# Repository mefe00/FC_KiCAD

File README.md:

# FC_KiCAD
Projede STM32F405RGT6 MCU, ICM-42688-P IMU, BMP388 basınç sensörü ve istenirse harici takılabilmesi için SPI çıkışı ve I2C çıkışı mevcuttur. Projenin yazılımı github hesabım üzerinde mevcuttur ve geliştirilme aşamasındadır.

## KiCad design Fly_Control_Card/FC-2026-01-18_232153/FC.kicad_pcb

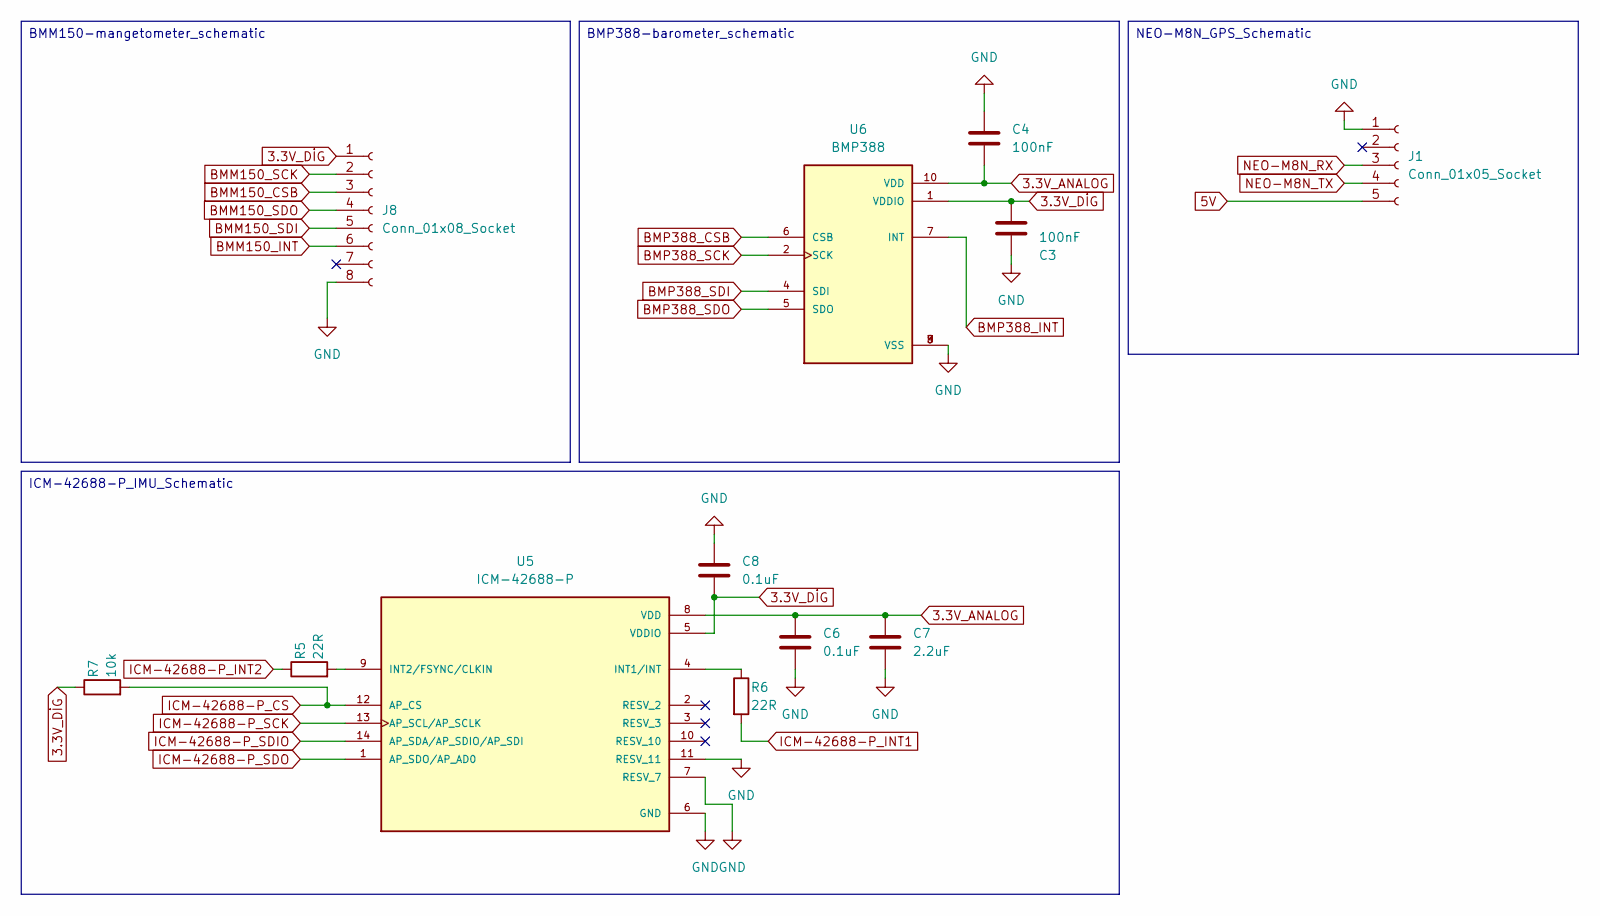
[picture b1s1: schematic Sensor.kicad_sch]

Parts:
C3, C4: 100nF; C_0402_1005Metric
C6, C8: 0.1uF; C_0402_1005Metric
C7: 2.2uF; C_0402_1005Metric
J1: Conn_01x05_Socket; JST_SH_SM05B-SRSS-TB_1x05-1MP_P1.00mm_Horizontal
J8: Conn_01x08_Socket; JST_SH_SM08B-SRSS-TB_1x08-1MP_P1.00mm_Horizontal
R5, R6: 22R; R_0402_1005Metric
R7: 10k; R_0402_1005Metric
U5: ICM-42688-P; PQFN50P300X250X97-14N; PARTREV 1.2
U6: BMP388; PQFN50P200X200X80-10N; PARTREV 1.1

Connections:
3.3V_ANALOG: C4.2, C6.1, C7.1, U5.8 (VDD), U6.10 (VDD); also elsewhere on the board
3.3V_DİG: C3.1, C8.2, J8.1, R7.1, U5.5 (VDDIO), U6.1 (VDDIO); also elsewhere on the board
5V: J1.5; also elsewhere on the board
BMM150_CSB: J8.3; also elsewhere on the board
BMM150_INT: J8.6; also elsewhere on the board
BMM150_SCK: J8.2; also elsewhere on the board
BMM150_SDI: J8.5; also elsewhere on the board
BMM150_SDO: J8.4; also elsewhere on the board
BMP388_CSB: U6.6 (CSB); also elsewhere on the board
BMP388_INT: U6.7 (INT); also elsewhere on the board
BMP388_SCK: U6.2 (SCK); also elsewhere on the board
BMP388_SDI: U6.4 (SDI); also elsewhere on the board
BMP388_SDO: U6.5 (SDO); also elsewhere on the board
GND: C3.2, C4.1, C6.2, C7.2, C8.1, J1.1, J8.8, U5.6 (GND), U5.7 (RESV_7), U5.11 (RESV_11), U6.3 (VSS), U6.8 (VSS), U6.9 (VSS); also elsewhere on the board
ICM-42688-P_CS: R7.2, U5.12 (AP_CS); also elsewhere on the board
ICM-42688-P_INT1: R6.2; also elsewhere on the board
ICM-42688-P_INT2: R5.1; also elsewhere on the board
ICM-42688-P_SCK: U5.13 (AP_SCL/AP_SCLK); also elsewhere on the board
ICM-42688-P_SDIO: U5.14 (AP_SDA/AP_SDIO/AP_SDI); also elsewhere on the board
ICM-42688-P_SDO: U5.1 (AP_SDO/AP_AD0); also elsewhere on the board
NEO-M8N_RX: J1.3; also elsewhere on the board
NEO-M8N_TX: J1.4; also elsewhere on the board
unnamed: R6.1, U5.4 (INT1/INT)
unnamed: R5.2, U5.9 (INT2/FSYNC/CLKIN)

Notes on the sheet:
BMP388-barometer_schematic
NEO-M8N_GPS_Schematic
BMM150-mangetometer_schematic
ICM-42688-P_IMU_Schematic

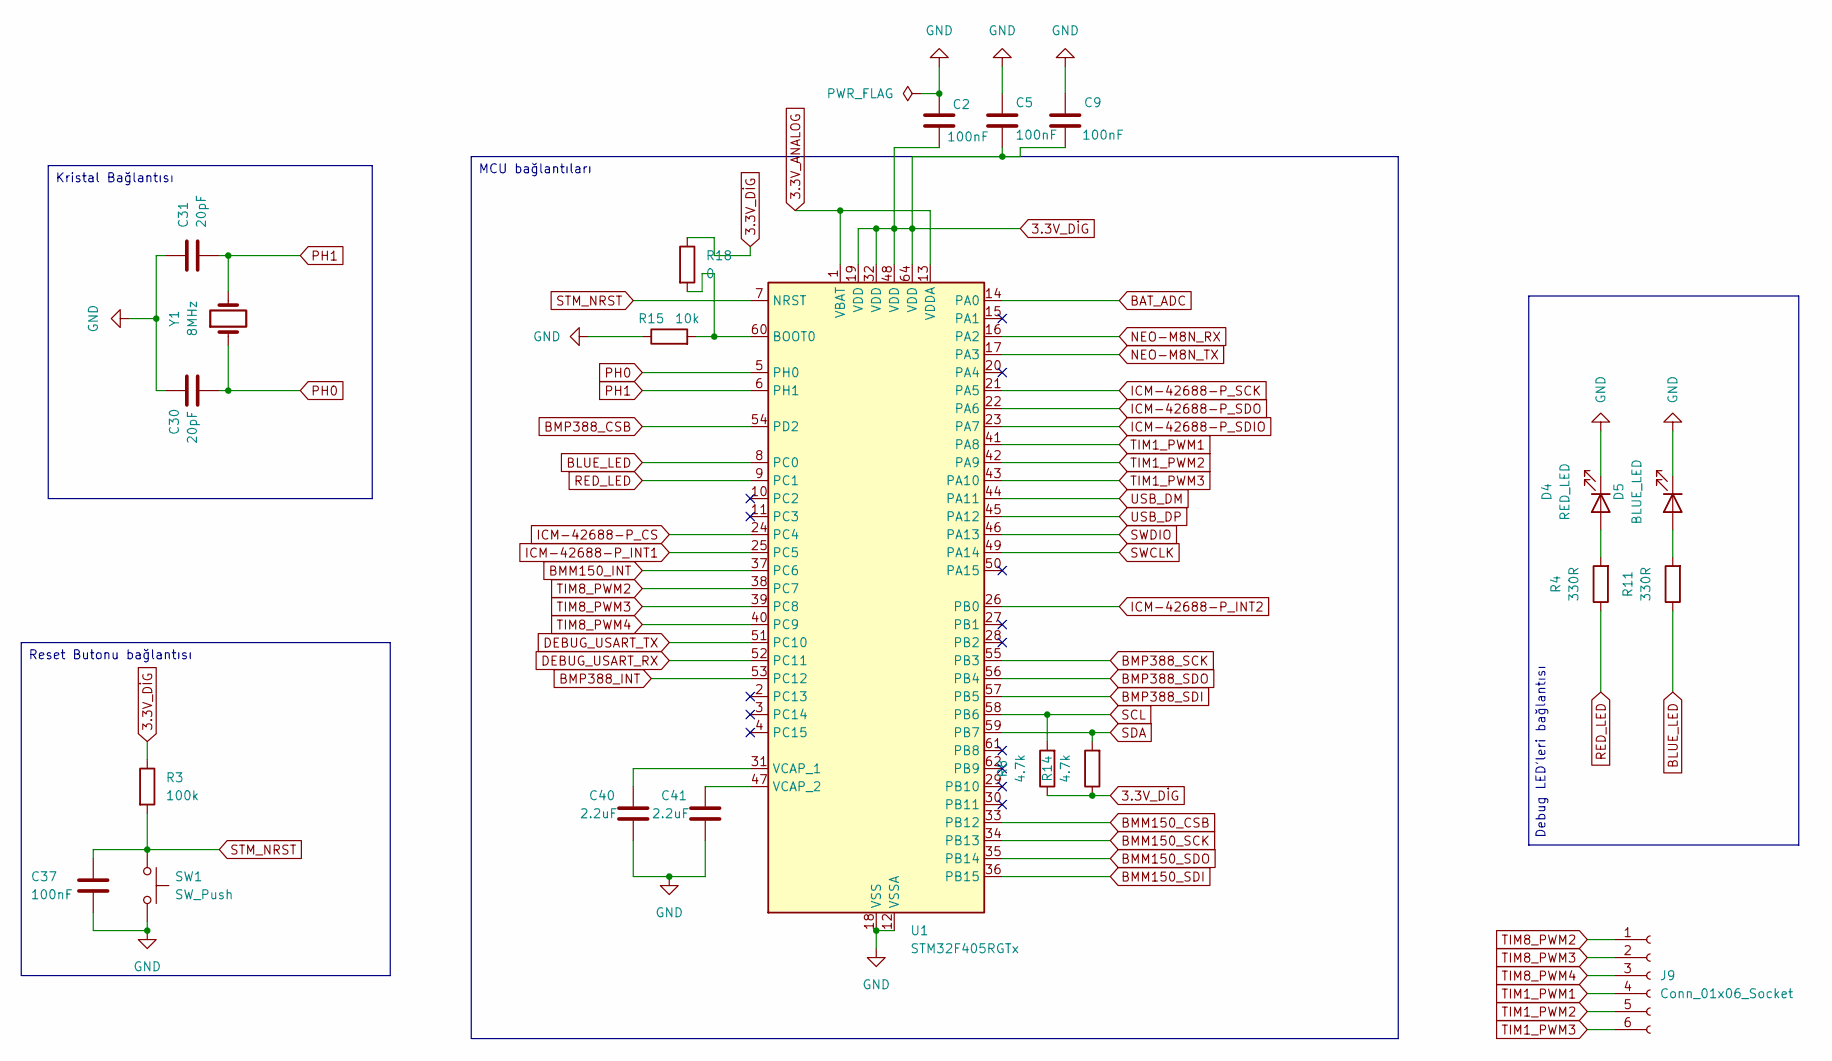
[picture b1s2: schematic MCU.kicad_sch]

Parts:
C2, C5, C9, C37: 100nF; C_0402_1005Metric
C30, C31: 20pF; C_0402_1005Metric
C40, C41: 2.2uF; C_0402_1005Metric
D4: RED_LED; LED_0603_1608Metric
D5: BLUE_LED; LED_0603_1608Metric
J9: Conn_01x06_Socket; JST_SH_SM06B-SRSS-TB_1x06-1MP_P1.00mm_Horizontal
R3: 100k; R_0402_1005Metric
R4, R11: 330R; R_0402_1005Metric
R8, R14: 4.7k; R_0402_1005Metric
R15: 10k; R_0402_1005Metric
R18: 0; R_0402_1005Metric
SW1: SW_Push; SW_Push_1P1T_NO_CK_KMR2
U1: STM32F405RGTx; LQFP-64_10x10mm_P0.5mm
Y1: 8MHz; Crystal_SMD_5032-2Pin_5.0x3.2mm

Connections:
3.3V_ANALOG: U1.1 (VBAT), U1.13 (VDDA); also elsewhere on the board
3.3V_DİG: C2.2, C5.2, C9.2, R3.1, R8.1, R14.1, R18.1, U1.19 (VDD), U1.32 (VDD), U1.48 (VDD), U1.64 (VDD); also elsewhere on the board
BAT_ADC: U1.14 (PA0); also elsewhere on the board
BLUE_LED: R11.1, U1.8 (PC0)
BMM150_CSB: U1.33 (PB12); also elsewhere on the board
BMM150_INT: U1.37 (PC6); also elsewhere on the board
BMM150_SCK: U1.34 (PB13); also elsewhere on the board
BMM150_SDI: U1.36 (PB15); also elsewhere on the board
BMM150_SDO: U1.35 (PB14); also elsewhere on the board
BMP388_CSB: U1.54 (PD2); also elsewhere on the board
BMP388_INT: U1.53 (PC12); also elsewhere on the board
BMP388_SCK: U1.55 (PB3); also elsewhere on the board
BMP388_SDI: U1.57 (PB5); also elsewhere on the board
BMP388_SDO: U1.56 (PB4); also elsewhere on the board
DEBUG_USART_RX: U1.52 (PC11); also elsewhere on the board
DEBUG_USART_TX: U1.51 (PC10); also elsewhere on the board
GND: C2.1, C5.1, C9.1, C30.1, C31.1, C37.2, C40.2, C41.2, D4.1 (K), D5.1 (K), R15.1, SW1.2, U1.12 (VSSA), U1.18 (VSS), U1.63 (VSS); also elsewhere on the board
ICM-42688-P_CS: U1.24 (PC4); also elsewhere on the board
ICM-42688-P_INT1: U1.25 (PC5); also elsewhere on the board
ICM-42688-P_INT2: U1.26 (PB0); also elsewhere on the board
ICM-42688-P_SCK: U1.21 (PA5); also elsewhere on the board
ICM-42688-P_SDIO: U1.23 (PA7); also elsewhere on the board
ICM-42688-P_SDO: U1.22 (PA6); also elsewhere on the board
NEO-M8N_RX: U1.16 (PA2); also elsewhere on the board
NEO-M8N_TX: U1.17 (PA3); also elsewhere on the board
unnamed: D4.2 (A), R4.2
unnamed: D5.2 (A), R11.2
unnamed: R15.2, R18.2, U1.60 (BOOT0)
unnamed: C40.1, U1.31 (VCAP_1)
unnamed: C41.1, U1.47 (VCAP_2)
PH0: C30.2, U1.5 (PH0), Y1.1
PH1: C31.2, U1.6 (PH1), Y1.2
RED_LED: R4.1, U1.9 (PC1)
SCL: R8.2, U1.58 (PB6); also elsewhere on the board
SDA: R14.2, U1.59 (PB7); also elsewhere on the board
STM_NRST: C37.1, R3.2, SW1.1, U1.7 (NRST)
SWCLK: U1.49 (PA14); also elsewhere on the board
SWDIO: U1.46 (PA13); also elsewhere on the board
TIM1_PWM1: J9.4, U1.41 (PA8)
TIM1_PWM2: J9.5, U1.42 (PA9)
TIM1_PWM3: J9.6, U1.43 (PA10)
TIM8_PWM2: J9.1, U1.38 (PC7)
TIM8_PWM3: J9.2, U1.39 (PC8)
TIM8_PWM4: J9.3, U1.40 (PC9)
USB_DM: U1.44 (PA11); also elsewhere on the board
USB_DP: U1.45 (PA12); also elsewhere on the board

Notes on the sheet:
Kristal Bağlantısı
Reset Butonu bağlantısı
Debug LED'leri bağlantısı
MCU bağlantıları

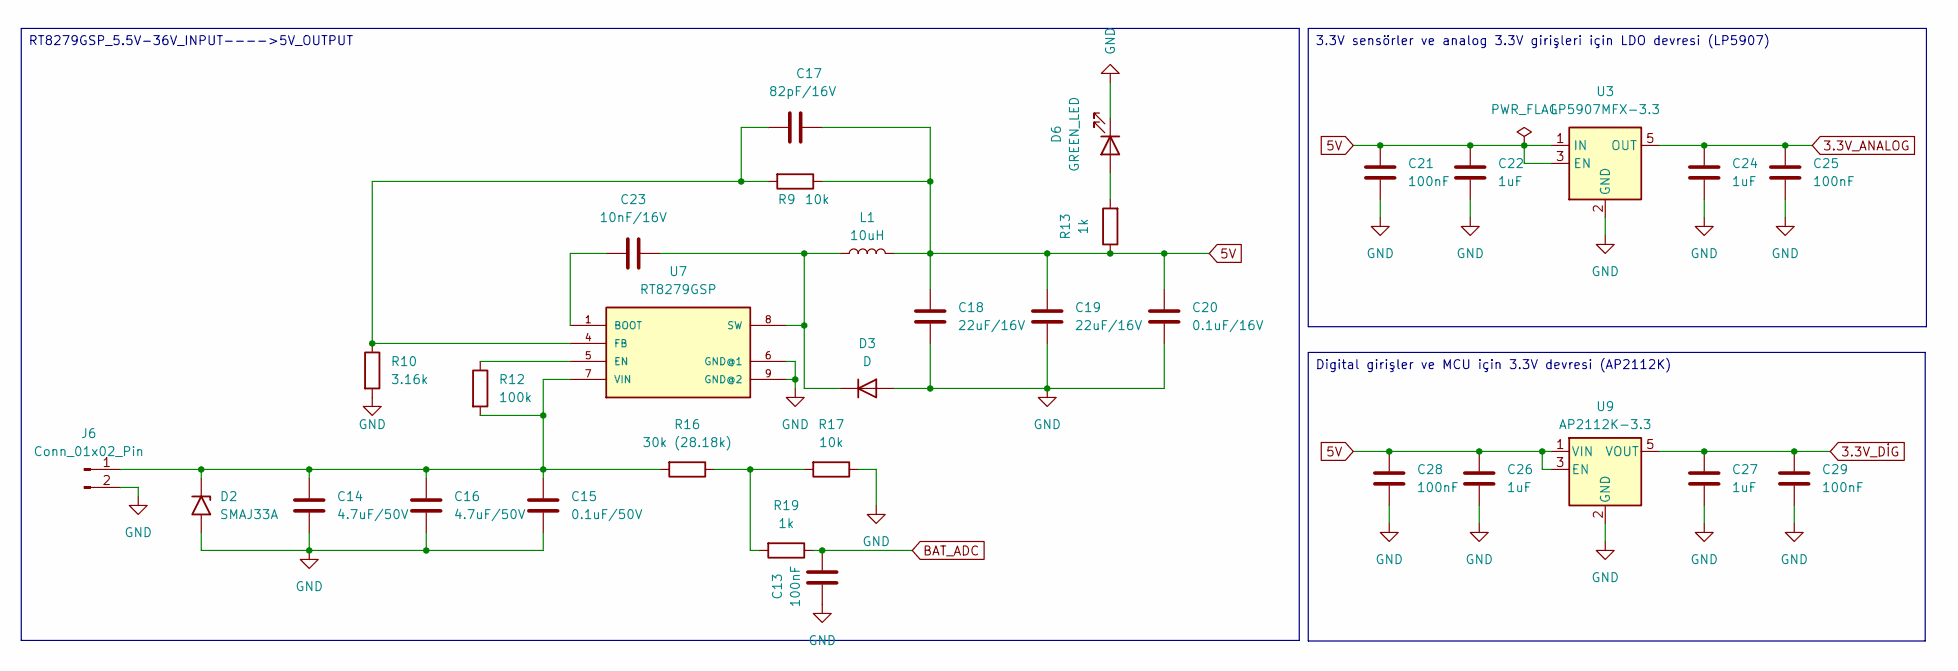
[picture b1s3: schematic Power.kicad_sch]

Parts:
C13, C21, C25, C28, C29: 100nF; C_0603_1608Metric
C14, C16: 4.7uF/50V; C_0603_1608Metric
C15: 0.1uF/50V; C_0603_1608Metric
C17: 82pF/16V; C_0603_1608Metric
C18, C19: 22uF/16V; C_0603_1608Metric
C20: 0.1uF/16V; C_0603_1608Metric
C22, C24, C26, C27: 1uF; C_0402_1005Metric
C23: 10nF/16V; C_0603_1608Metric
D2: SMAJ33A; D_SMA
D3: D; D_SMC
D6: GREEN_LED; LED_0603_1608Metric
J6: Conn_01x02_Pin; SolderWire-0.1sqmm_1x02_P3.6mm_D0.4mm_OD1mm
L1: 10uH; L_APV_ANR4026
R9: 10k; R_0603_1608Metric
R10: 3.16k; R_0603_1608Metric
R12: 100k; R_0603_1608Metric
R13: 1k; R_0402_1005Metric
R16: 30k (28.18k); R_0805_2012Metric
R17: 10k; R_0805_2012Metric
R19: 1k; R_0805_2012Metric
U3: LP5907MFX-3.3; SOT-23-5
U7: RT8279GSP; SOIC127P600X175-9N
U9: AP2112K-3.3; SOT-23-5

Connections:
3.3V_ANALOG: C24.1, C25.1, U3.5 (OUT); also elsewhere on the board
3.3V_DİG: C27.1, C29.1, U9.5 (VOUT); also elsewhere on the board
5V: C17.1, C18.1, C19.1, C20.1, C21.1, C22.1, C26.1, C28.1, L1.2, R9.1, R13.1, U3.1 (IN), U3.3 (EN), U9.1 (VIN), U9.3 (EN); also elsewhere on the board
BAT_ADC: C13.2, R19.1; also elsewhere on the board
GND: C13.1, C14.2, C15.2, C16.2, C18.2, C19.2, C20.2, C21.2, C22.2, C24.2, C25.2, C26.2, C27.2, C28.2, C29.2, D2.2 (A2), D3.2 (A), D6.1 (K), J6.2, R10.2, R17.1, U3.2 (GND), U7.6 (GND@1), U7.9 (GND@2), U9.2 (GND); also elsewhere on the board
unnamed: C14.1, C15.1, C16.1, D2.1 (A1), J6.1, R12.2, R16.2, U7.7 (VIN)
unnamed: C23.2, D3.1 (K), L1.1, U7.8 (SW)
unnamed: D6.2 (A), R13.2
unnamed: R16.1, R17.2, R19.2
unnamed: C23.1, U7.1 (BOOT)
unnamed: R12.1, U7.5 (EN)
unnamed: C17.2, R9.2, R10.1, U7.4 (FB)

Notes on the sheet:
3.3V sensörler ve analog 3.3V girişleri için LDO devresi (LP5907)
RT8279GSP_5.5V-36V_INPUT---->5V_OUTPUT
Digital girişler ve MCU için 3.3V devresi (AP2112K)

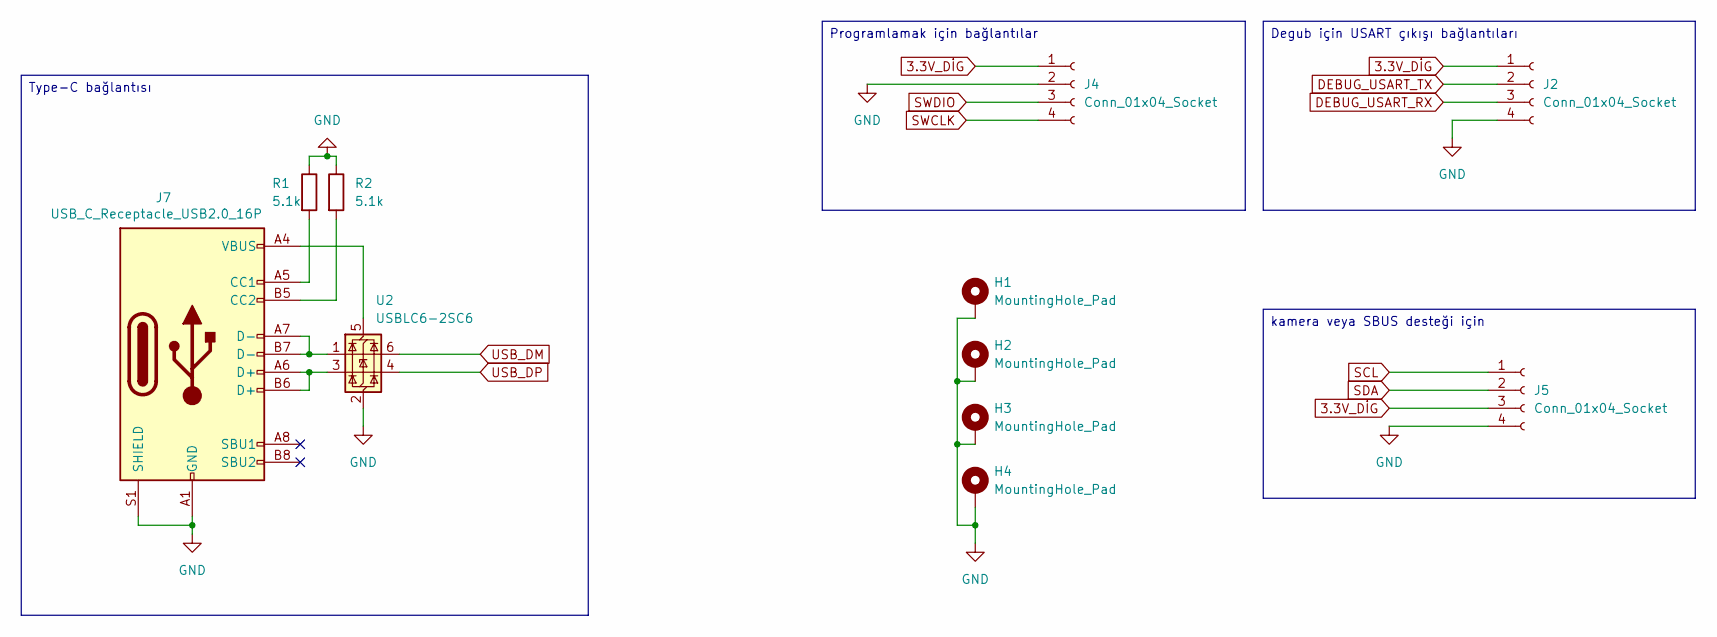
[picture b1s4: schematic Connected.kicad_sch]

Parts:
H1, H2, H3, H4: MountingHole_Pad; MountingHole_3.2mm_M3_Pad_Via
J2, J4, J5: Conn_01x04_Socket; JST_SH_SM04B-SRSS-TB_1x04-1MP_P1.00mm_Horizontal
J7: USB_C_Receptacle_USB2.0_16P; USB_C_Receptacle_GCT_USB4105-xx-A_16P_TopMnt_Horizontal
R1, R2: 5.1k; R_0402_1005Metric
U2: USBLC6-2SC6; SOT-23-6

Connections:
3.3V_DİG: J2.1, J4.1, J5.3; also elsewhere on the board
DEBUG_USART_RX: J2.3; also elsewhere on the board
DEBUG_USART_TX: J2.2; also elsewhere on the board
GND: H1.1, H2.1, H3.1, H4.1, J2.4, J4.2, J5.4, J7.A1 (GND), J7.A12 (GND), J7.B1 (GND), J7.B12 (GND), J7.S1 (SHIELD), R1.1, R2.1, U2.2 (GND); also elsewhere on the board
unnamed: J7.A5 (CC1), R1.2
unnamed: J7.B5 (CC2), R2.2
unnamed: J7.A6 (D+), J7.B6 (D+), U2.3 (I/O2)
unnamed: J7.A7 (D-), J7.B7 (D-), U2.1 (I/O1)
unnamed: J7.A4 (VBUS), J7.A9 (VBUS), J7.B4 (VBUS), J7.B9 (VBUS), U2.5 (VBUS)
SCL: J5.1; also elsewhere on the board
SDA: J5.2; also elsewhere on the board
SWCLK: J4.4; also elsewhere on the board
SWDIO: J4.3; also elsewhere on the board
USB_DM: U2.6 (I/O1); also elsewhere on the board
USB_DP: U2.4 (I/O2); also elsewhere on the board

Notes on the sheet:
Degub için USART çıkışı bağlantıları
kamera veya SBUS desteği için
Programlamak için bağlantılar
Type-C bağlantısı

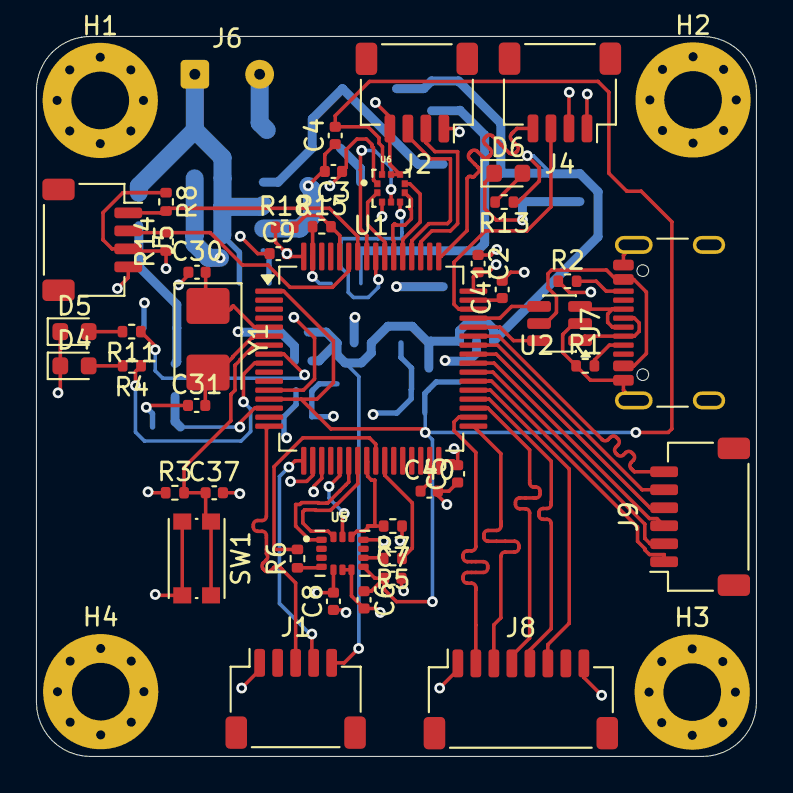
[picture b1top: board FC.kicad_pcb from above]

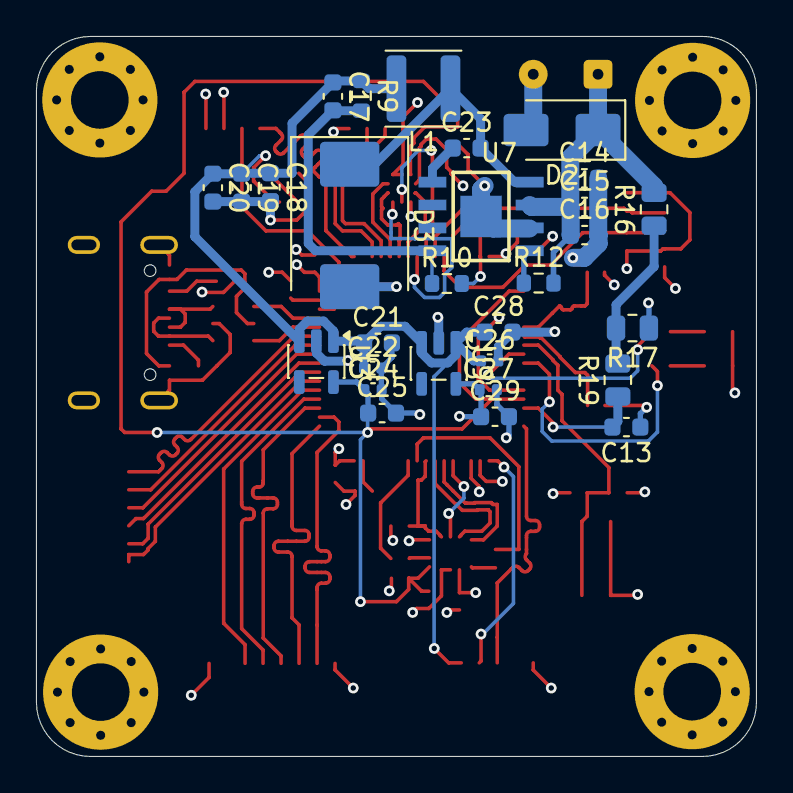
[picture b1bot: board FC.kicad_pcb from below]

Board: 4 copper layers, 40.0 x 40.0 mm, 76 parts (29 on the bottom side), 61 nets.

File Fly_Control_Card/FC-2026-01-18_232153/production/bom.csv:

Designator,Footprint,Quantity,Value,LCSC Part #
"C13, C21, C25, C28, C29",0603,5,100nF,
"C14, C16",0603,2,4.7uF/50V,
C15,0603,1,0.1uF/50V,
C17,0603,1,82pF/16V,
"C18, C19",0603,2,22uF/16V,
"C2, C3, C37, C4, C5, C9",0402,6,100nF,
C20,0603,1,0.1uF/16V,
"C22, C24, C26, C27",0402,4,1uF,
C23,0603,1,10nF/16V,
"C30, C31",0402,2,20pF,
"C40, C41, C7",0402,3,2.2uF,
"C6, C8",0402,2,0.1uF,
D2,D_SMA,1,SMAJ33A,
D3,D_SMC,1,D,
D4,0603,1,RED_LED,
D5,0603,1,BLUE_LED,
D6,0603,1,GREEN_LED,
J1,JST_SH_SM05B-SRSS-TB_1x05-1MP_P1.00mm_Horizontal,1,Conn_01x05_Socket,
"J2, J4, J5",JST_SH_SM04B-SRSS-TB_1x04-1MP_P1.00mm_Horizontal,3,Conn_01x04_Socket,
J6,SolderWire-0.1sqmm_1x02_P3.6mm_D0.4mm_OD1mm,1,Conn_01x02_Pin,
J7,USB_C_Receptacle_GCT_USB4105-xx-A_16P_TopMnt_Horizontal,1,USB_C_Receptacle_USB2.0_16P,
J8,JST_SH_SM08B-SRSS-TB_1x08-1MP_P1.00mm_Horizontal,1,Conn_01x08_Socket,
J9,JST_SH_SM06B-SRSS-TB_1x06-1MP_P1.00mm_Horizontal,1,Conn_01x06_Socket,
L1,L_APV_ANR4026,1,10uH,
"R1, R2",0402,2,5.1k,
R10,0603,1,3.16k,
"R11, R4",0402,2,330R,
R12,0603,1,100k,
R13,0402,1,1k,
"R14, R8",0402,2,4.7k,
"R15, R7",0402,2,10k,
R16,0805,1,30k (28.18k),
R17,0805,1,10k,
R18,0402,1,0,
R19,0805,1,1k,
R3,0402,1,100k,
"R5, R6",0402,2,22R,
R9,0603,1,10k,
SW1,SW_Push_1P1T_NO_CK_KMR2,1,SW_Push,
U1,LQFP-64_10x10mm_P0.5mm,1,STM32F405RGTx,
U2,SOT-23-6,1,USBLC6-2SC6,
U3,SOT-23-5,1,LP5907MFX-3.3,
U5,PQFN50P300X250X97-14N,1,ICM-42688-P,
U6,PQFN50P200X200X80-10N,1,BMP388,
U7,SOIC127P600X175-9N,1,RT8279GSP,
U9,SOT-23-5,1,AP2112K-3.3,
Y1,Crystal_SMD_5032-2Pin_5.0x3.2mm,1,8MHz,

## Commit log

2026-01-31 Add images to README for project visualization
    Added images to enhance project documentation.
